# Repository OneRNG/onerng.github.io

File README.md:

onerng.github.io
================

OneRNG - Hardware Random Number Generator

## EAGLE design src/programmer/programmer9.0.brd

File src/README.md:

onerng.github.io
================

onerng.info
-----------

These are the source files for the onerng.info website, hosted on github.

OneRNG - Hardware Random Number Generator

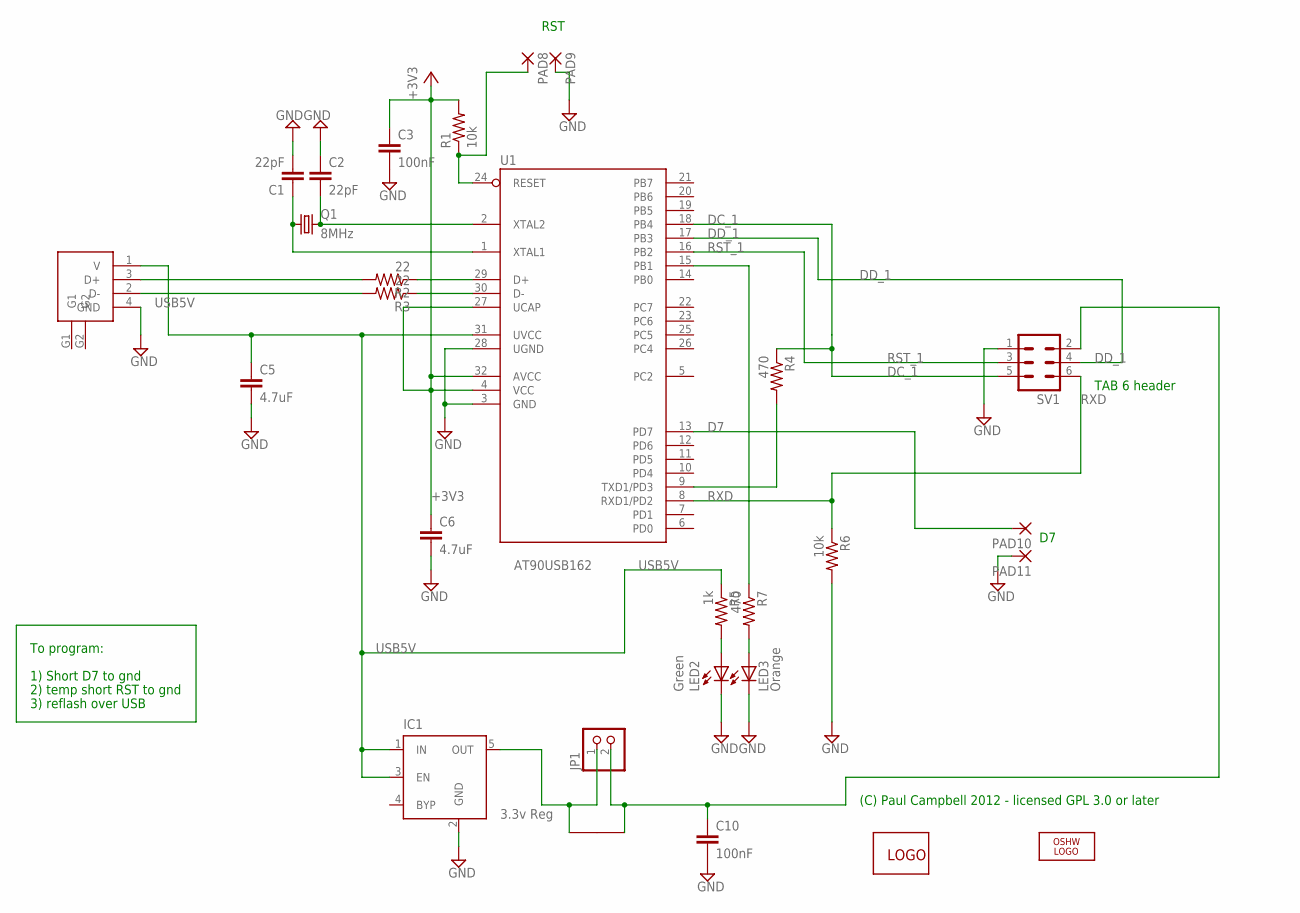
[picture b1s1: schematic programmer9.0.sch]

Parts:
C1, C2: 22pF; C0603
C3, C10: 100nF; C0603
C5, C6: 4.7uF; C0805
IC1: 3.3v Reg; SOT23-5
JP1: PINHD-1X2; 1X02
LED2: Green; CHIP-LED0805
LED3: Orange; CHIP-LED0805
LOGO2: OSHW_LOGO_FILLX0100-NT; OSHW_FILLX100_NOTEXT
PAD8, PAD9, PAD10, PAD11: 1,6/0,8
Q1: 8MHz; HC49UP
R1, R6: 10k; R0603
R2, R3: 22; R0603
R4, R7: 470; R0603
R5: 1k; R0603
SV1: MA03-2
U1: AT90USB162; TQFP32-08
U$1: LINK
U$2: MOONBASE-LOGO
U$3: USB-RAW; USBY

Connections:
+3V3: C3.1, C6.1, R1.2, U1.4 (VCC), U1.27 (UCAP), U1.32 (AVCC)
D7: PAD10.1, U1.13 (PD7)
DC_1: R4.1, SV1.5, U1.18 (PB4)
DD_1: SV1.4, U1.17 (PB3)
GND: C1.2, C2.1, C3.2, C5.2, C6.2, C10.2, IC1.2 (GND), LED2.C, LED3.C, PAD9.1, PAD11.1, R6.2, SV1.1, U1.3 (GND), U1.28 (UGND), U$3.4 (GND)
unnamed: C1.1, Q1.1, U1.1 (XTAL1)
unnamed: C2.2, Q1.2, U1.2 (XTAL2)
unnamed: R2.1, U1.29 (D+)
unnamed: R3.1, U1.30 (D-)
unnamed: R4.2, U1.9 (TXD1/PD3)
unnamed: IC1.5 (OUT), JP1.1, U$1.1
unnamed: C10.1, JP1.2, SV1.2, U$1.2
unnamed: R3.2, U$3.2 (D-)
unnamed: R2.2, U$3.3 (D+)
unnamed: LED2.A, R5.2
unnamed: LED3.A, R7.2
unnamed: R7.1, U1.15 (PB1)
RST: PAD8.1, R1.1, U1.24 (RESET)
RST_1: SV1.3, U1.16 (PB2)
RXD: R6.1, SV1.6, U1.8 (RXD1/PD2)
USB5V: C5.1, IC1.1 (IN), IC1.3 (EN), R5.1, U1.31 (UVCC), U$3.1 (V)

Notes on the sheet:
(C) Paul Campbell 2012 - licensed GPL 3.0 or later
RST
To program:
1) Short D7 to gnd
2) temp short RST to gnd
3) reflash over USB
TAB 6 header

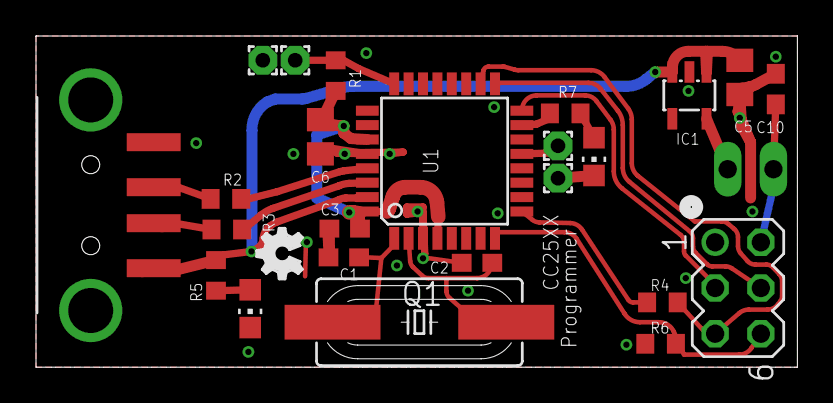
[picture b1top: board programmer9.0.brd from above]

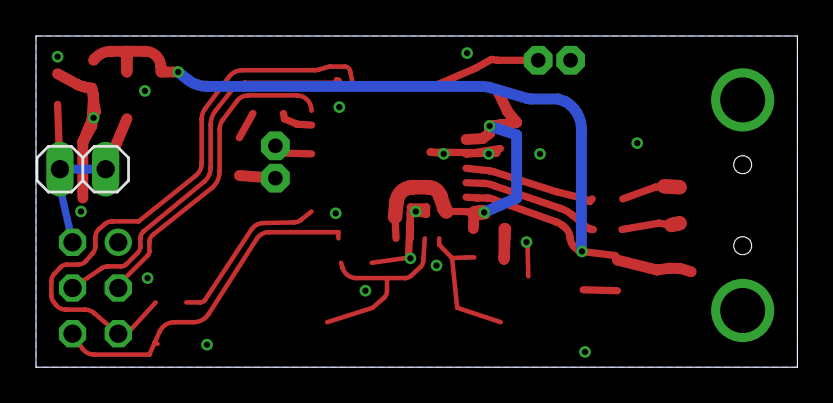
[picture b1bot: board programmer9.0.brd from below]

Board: 2 copper layers, 42.3 x 18.4 mm, 28 parts (2 on the bottom side), 21 nets.

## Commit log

2013-12-28 Initial website main page
    The first real page, describing the project in a couple of sentences and publishing the team members.
2013-12-29 CNAME instructions for pages.github.io
    None of that www stuff here ... just a straight short domain name
2014-01-09 Small update to contact details
    Basically asking people to contact Jim for general queries
2014-01-22 Added a photo of the latest prototype
2014-01-22 Image was a JPG, not a PNG :-) And a little too big, too.
2014-01-22 Added the image to the site ... silly me
2014-06-04 Added styles, images and fonts to the site. Updated text with the current position of the project.
2014-06-05 Fixed local font assignment
2014-06-05 Added random-order dice images via javascript
2014-06-23 Added more intro text
2014-06-23 Currently unlinked; beginnings of a long discussion about the technology
2014-07-02 Added span for OneRNG product name
2014-07-02 Longer introduction, started placeholding links to more pages
2014-07-02 Initial page on Random & Entropy
2014-07-03 Added Open What discussion page and logos
2014-07-03 A couple of new CSS options
2014-07-03 Page on Trust and NSA badness
2014-07-03 More page links, and some style updates
2014-09-06 Refactored website to have HTML generated by Template::Toolkit (TT2)
    TT2 files live in the src/ directory, and *.tt2 files are processed to
    produce matching ../*.html.
    Also took the opportunity to change the CSS and visual appearance of the
    site. The HTML content "looks" the same, but has changed some internal structure
    because it is now being generated by TT2
2014-09-06 Shortened header text
2014-09-06 Clarified validation of hardware
2014-09-07 Wrapped dice output in a div
2014-09-07 Don't be afraid of BadUSB
2014-09-07 Moved BadUSB to a separate bulletpoint
2014-09-16 Image assets now live in src/
2014-09-16 Per-image info pages
2014-09-16 Switching to good old Makefile to build site
2014-09-16 More content on index, plus better footer
2014-09-16 New website version from src content changes
2014-09-17 Make cp operations verbose and fire on updates only
2014-09-17 Created smaller images for the index page
2014-09-17 Provided image size info on image asset pages
2014-10-29 Initial modifications for proposed Oct29 update
2014-10-29 Updated README.md to make sure readers know that this is just the website
2014-11-18 Added Roadmap section
2014-11-18 Fixed up external resources and some bio details on index page
2014-11-22 No more beta units available, so sad :-(
2014-11-22 Name-dropping in the roadmap
2014-12-16 Included Kickstarter, and HW/FW links
2014-12-16 Build updates timestamps ...
2015-01-14 LCA slides/current
2015-02-21 Large changes to make v2 site
2015-02-22 Added image titles
2015-02-22 Fixed a missing quote :-(
2015-03-24 Changed site header to make absolute references to css,js
2015-03-24 Added a subdir to get clean URLs
2015-03-24 Fixed footer absolute URLs, added link to GitHub
2015-03-24 Updating installation instructions
2015-03-24 Missed a couple of closing tags
2015-03-25 Restructured the OneRNG product page, added 3 images
2015-03-25 Added Programmer, and reformatted instructions page
2015-03-26 Reorganised image assets, added sw
2015-03-26 Expanded copyright comment in footer; removed render comment
2015-03-31 Moved programmer info from onerng/ to programmer/ and populated
2015-03-31 Updated footer
2015-03-31 Changed footer again
2015-03-31 Improved verify/use pages for onerng and programmer
2015-03-31 Fixed table width
2015-04-08 Typo in RPM package link, fixed
2015-04-09 Renamed a V2 image to be a V1 image
2015-04-15 Automated sw/ handling of deb, rpm, gz to detail the latest version Updated the CSS to display install commands Removed the old temporary catchall verify page
2015-04-15 Moved Host Software download location to https://github...
2015-04-19 SW v3.2 released, mkswtt sort fault fixed
2015-04-20 New SW version
2015-05-30 Updated shop forecast
2015-06-04 Released AusCERT2015 slides
2015-06-11 New photos for V2 internal, and a link to moonbaseotago for it
2015-06-15 Added instructions on installing the internal v2 unit
2015-06-15 Tidied up footer content and presentation
2015-06-21 Linux software v3.4 released
2015-07-07 Update to Current Status
2015-12-07 Added links to moonbase.tictail.com
2015-12-07 Typo in Moonbase's name
2015-12-07 Updated eshop link presentation/description
2015-12-07 New icon for Buy it Now section
2016-10-30 first pass rewrite
2016-11-09 Using modd and devd for the development workflow. Not important for production
2016-11-09 refreshed site
2016-11-27 Fixed orientation of image
2017-01-17 Added v3 images and availabililty comment
2017-01-17 Build for previous checkin
2017-01-18 Added V3 layout diagrams, and re-oriented photos of others to fit
2017-01-18 Built site as per previous checkin
2017-01-22 Host software v3.5 added
2017-01-22 Host software v3.5 added; site built
2017-02-05 Arch needs atd as well as at - extend installation instructions
2017-02-11 Fix for a link I broke with an over-enthuiastic search/replace
2017-02-11 Fix for a link I broke with an over-enthuiastic search/replace; built
2017-10-03 New firmware version, 3.6
2018-07-30 Sometimes rm -f caused Make to break; rm -rf is more appropriate
2019-03-25 Some minor changes, plus an update to the shop URL
2022-03-24 Changed Email List URL. Also some build tools changed their output a little for image info
2022-04-25 added changes for 3.7 - kernel RNG changes and python3 support
2022-04-25 run makefile
2022-04-25 fix typo
